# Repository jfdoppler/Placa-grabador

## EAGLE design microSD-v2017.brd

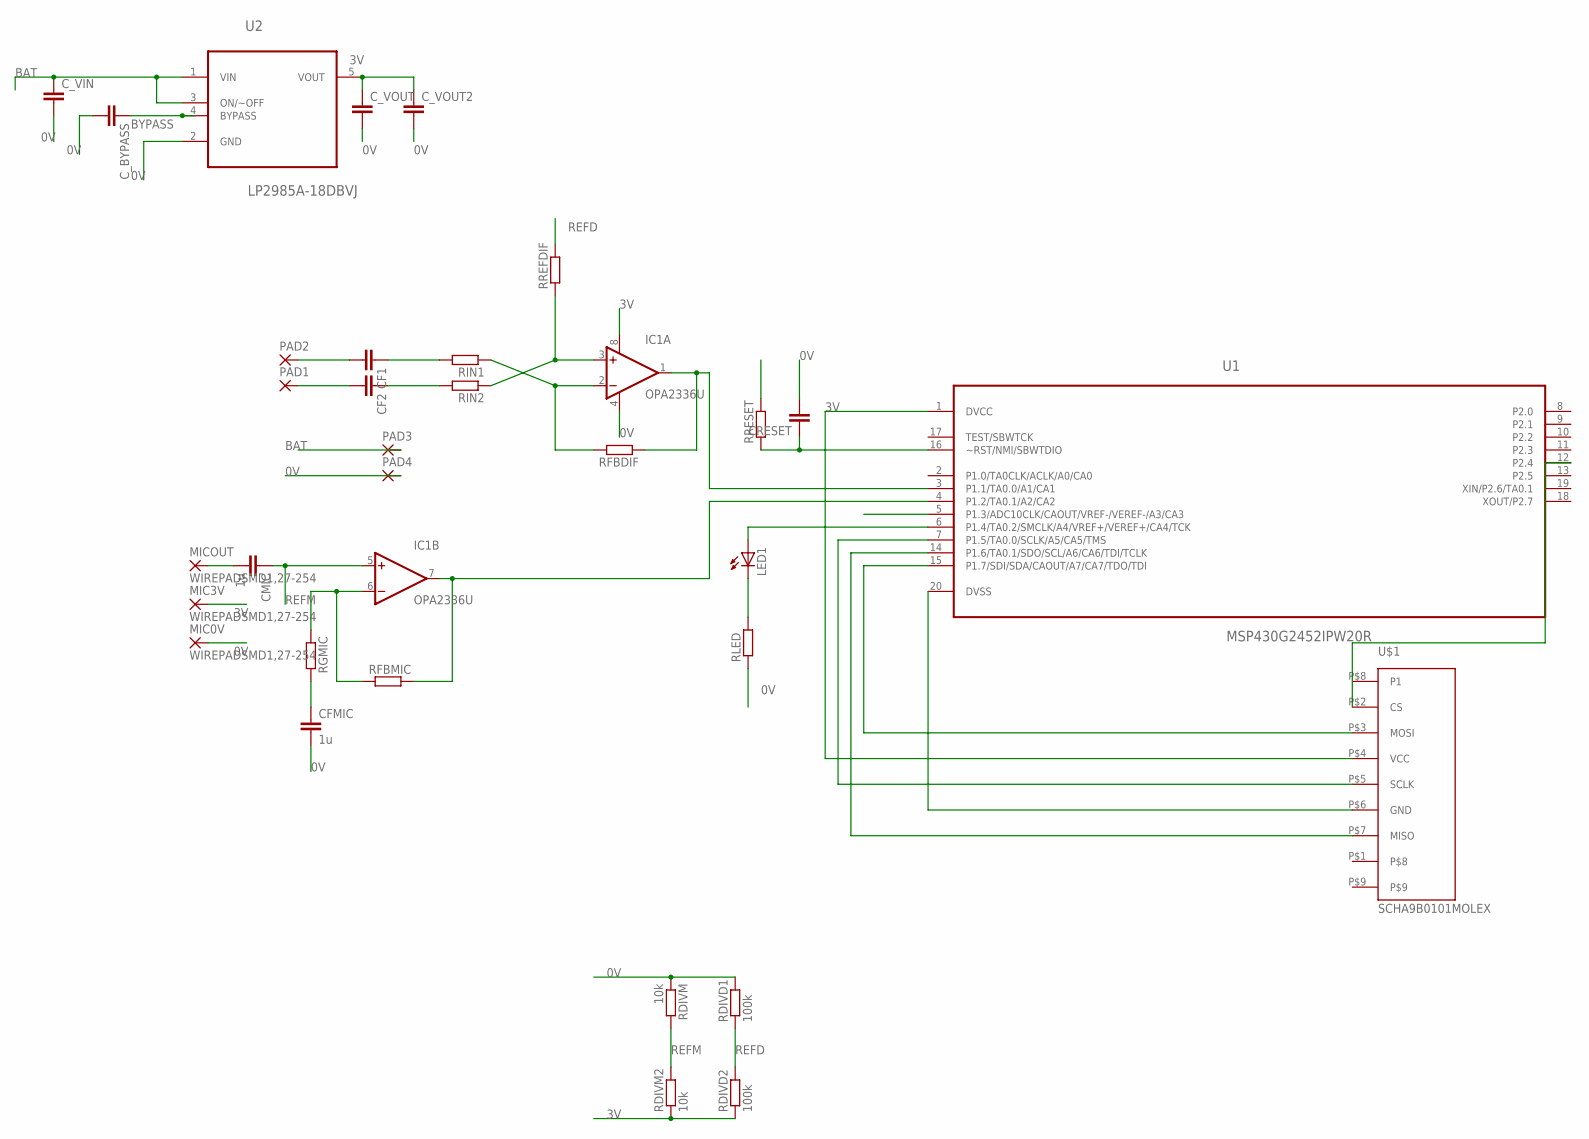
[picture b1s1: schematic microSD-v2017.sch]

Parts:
CF1, CF2: C; C0805
CFMIC: 1u; C0805
CMIC: 1u; C0805
CRESET: C; C0805
C_BYPASS: C; C0805
C_VIN: C; C0805
C_VOUT, C_VOUT2: C; C0805
IC1: OPA2336U; SO08
LED1: LED_ESML0603; LED_SML0603
MIC0V, MIC3V: WIREPADSMD1,27-254; SMD1,27-2,54
MICOUT: WIREPADSMD1,27-254; SMD1,27-2,54
PAD1, PAD2, PAD3, PAD4: SMD2; SMD1,27-2,54
RDIVD1, RDIVD2: 100k; R0805
RDIVM, RDIVM2: 10k; R0805
RFBDIF: R; R0805
RFBMIC: R; R0805
RGMIC: R; R0805
RIN1, RIN2: R; R0805
RLED: RR0603; R0603
RREFDIF: R; R0805
RRESET: R; R0805
U1: MSP430G2452IPW20R; SOP65P640X120-20N
U2: LP2985A-18DBVJ; SOT95P280X145-5N
U$1: SCHA9B0101MOLEX; SMD-MOLEX

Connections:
0V: CFMIC.2, CRESET.2, C_BYPASS.2, C_VIN.2, C_VOUT.2, C_VOUT2.2, IC1.4 (V-), MIC0V.1, PAD4.1, RDIVD1.2, RDIVM.1, RLED.1, U1.20 (DVSS), U2.2 (GND), U$1.P$6 (GND)
3V: C_VOUT.1, C_VOUT2.1, IC1.8 (V+), MIC3V.1, RDIVD2.1, RDIVM2.1, RRESET.2, U1.1 (DVCC), U2.5 (VOUT), U$1.P$4 (VCC)
BAT: C_VIN.1, PAD3.1, U2.1 (VIN), U2.3 (ON/~OFF)
BYPASS: C_BYPASS.1, U2.4 (BYPASS)
LED: LED1.A, U1.6 (P1.4/TA0.2/SMCLK/A4/VREF+/VEREF+/CA4/TCK)
unnamed: CF1.1, RIN1.2
unnamed: CF2.1, RIN2.2
unnamed: IC1.3 (+IN), RIN2.1, RREFDIF.1
unnamed: CRESET.1, RRESET.1, U1.16 (~RST/NMI/SBWTDIO)
unnamed: CF1.2, PAD2.1
unnamed: CF2.2, PAD1.1
unnamed: LED1.C, RLED.2
unnamed: CMIC.2, MICOUT.1
unnamed: U1.7 (P1.5/TA0.0/SCLK/A5/CA5/TMS), U$1.P$5 (SCLK)
unnamed: IC1.2 (-IN), RFBDIF.2, RIN1.1
unnamed: U1.14 (P1.6/TA0.1/SDO/SCL/A6/CA6/TDI/TCLK), U$1.P$7 (MISO)
unnamed: U1.15 (P1.7/SDI/SDA/CAOUT/A7/CA7/TDO/TDI), U$1.P$3 (MOSI)
unnamed: U1.12 (P2.4), U$1.P$2 (CS)
unnamed: IC1.6 (-IN), RFBMIC.1, RGMIC.1
unnamed: CFMIC.1, RGMIC.2
OUTDIF: IC1.1 (OUT), RFBDIF.1, U1.3 (P1.1/TA0.0/A1/CA1)
OUTMIC: IC1.7 (OUT), RFBMIC.2, U1.4 (P1.2/TA0.1/A2/CA2)
REFD: RDIVD1.1, RDIVD2.2, RREFDIF.2
REFM: CMIC.1, IC1.5 (+IN), RDIVM.2, RDIVM2.2

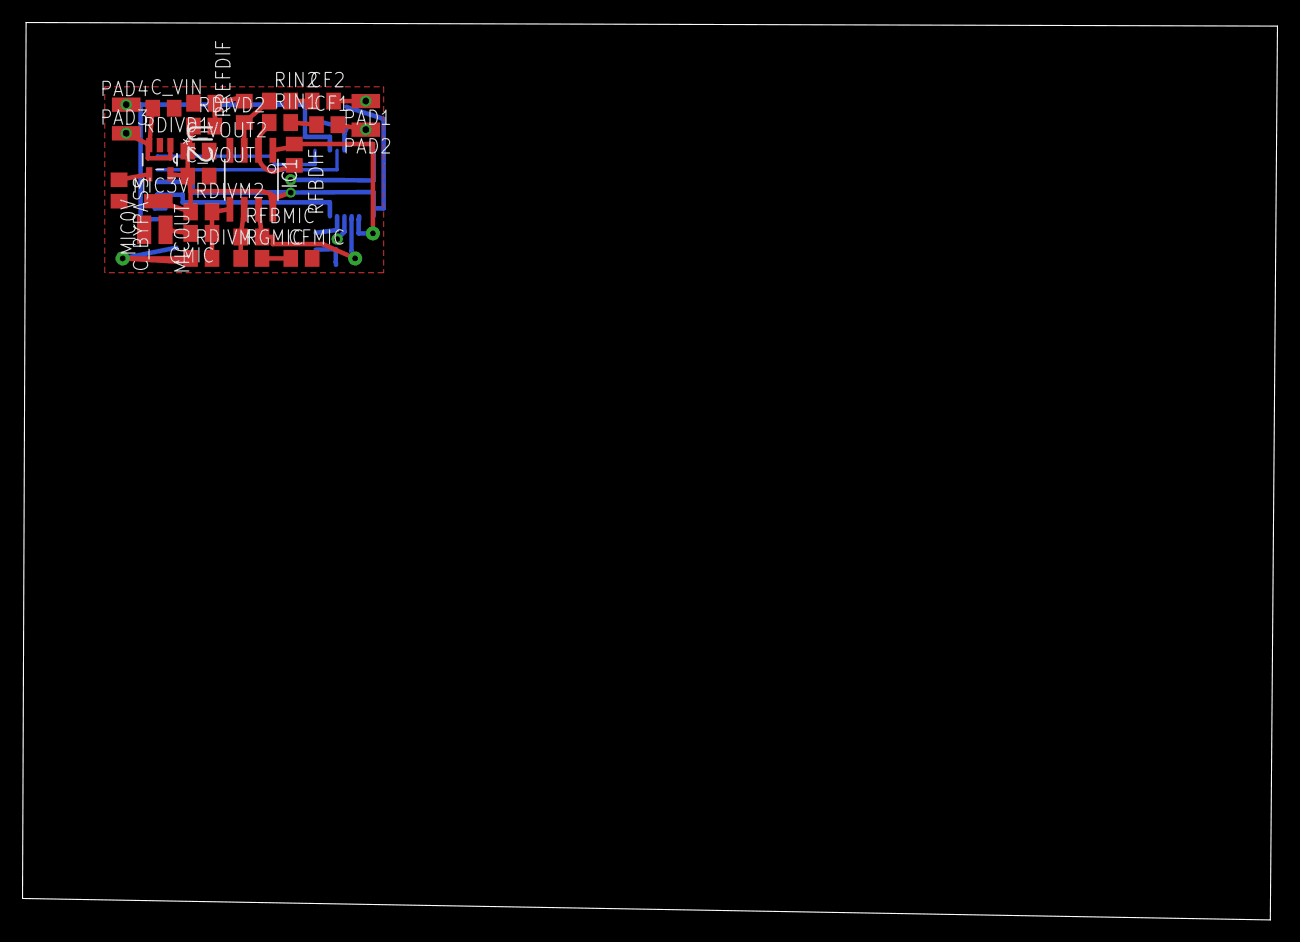
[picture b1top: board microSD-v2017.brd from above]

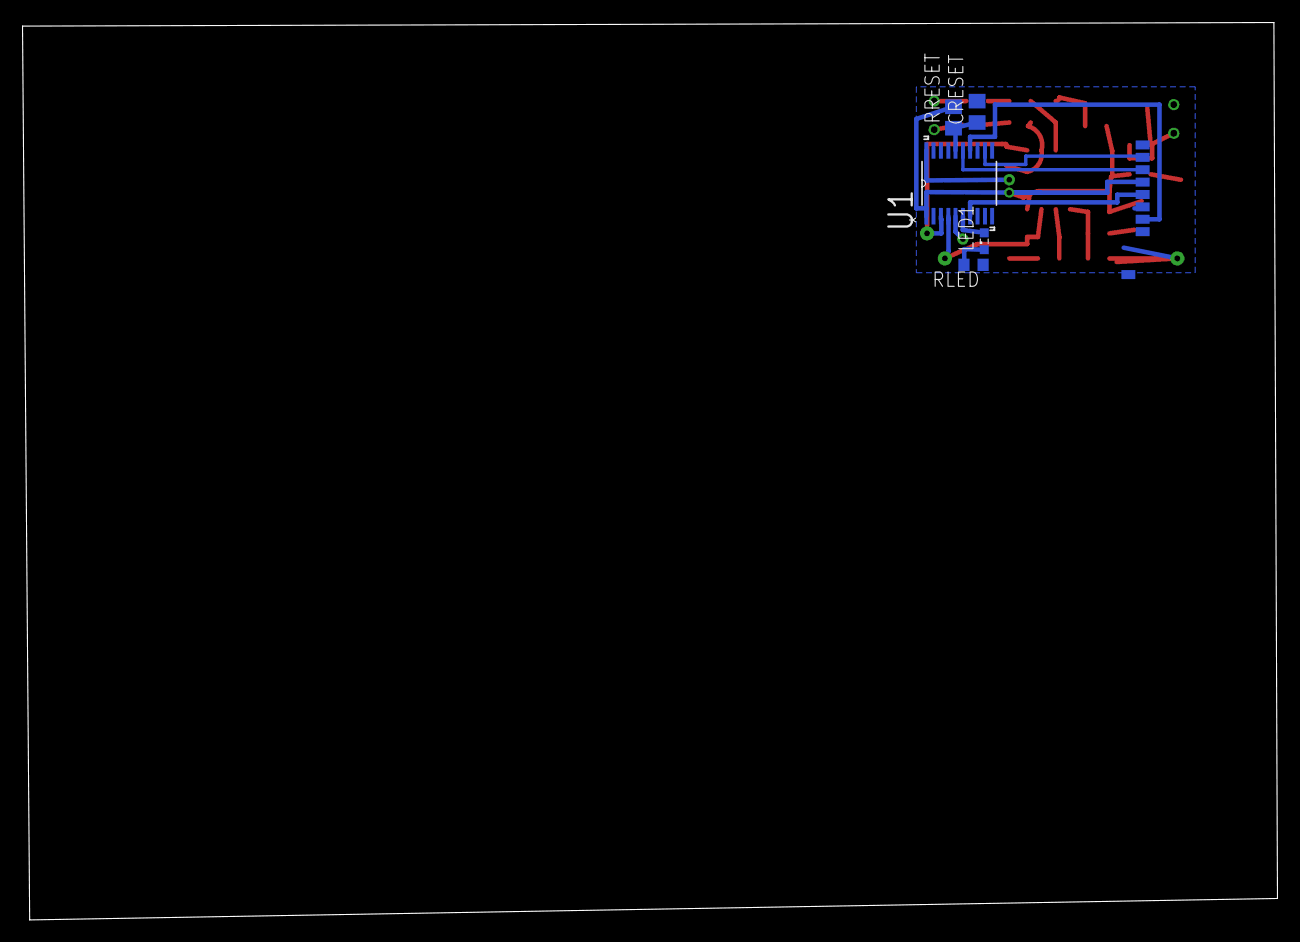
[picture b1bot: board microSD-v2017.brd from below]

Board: 2 copper layers, 111.4 x 79.7 mm, 33 parts (6 on the bottom side), 24 nets.

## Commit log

2019-03-22 Commit inicial
